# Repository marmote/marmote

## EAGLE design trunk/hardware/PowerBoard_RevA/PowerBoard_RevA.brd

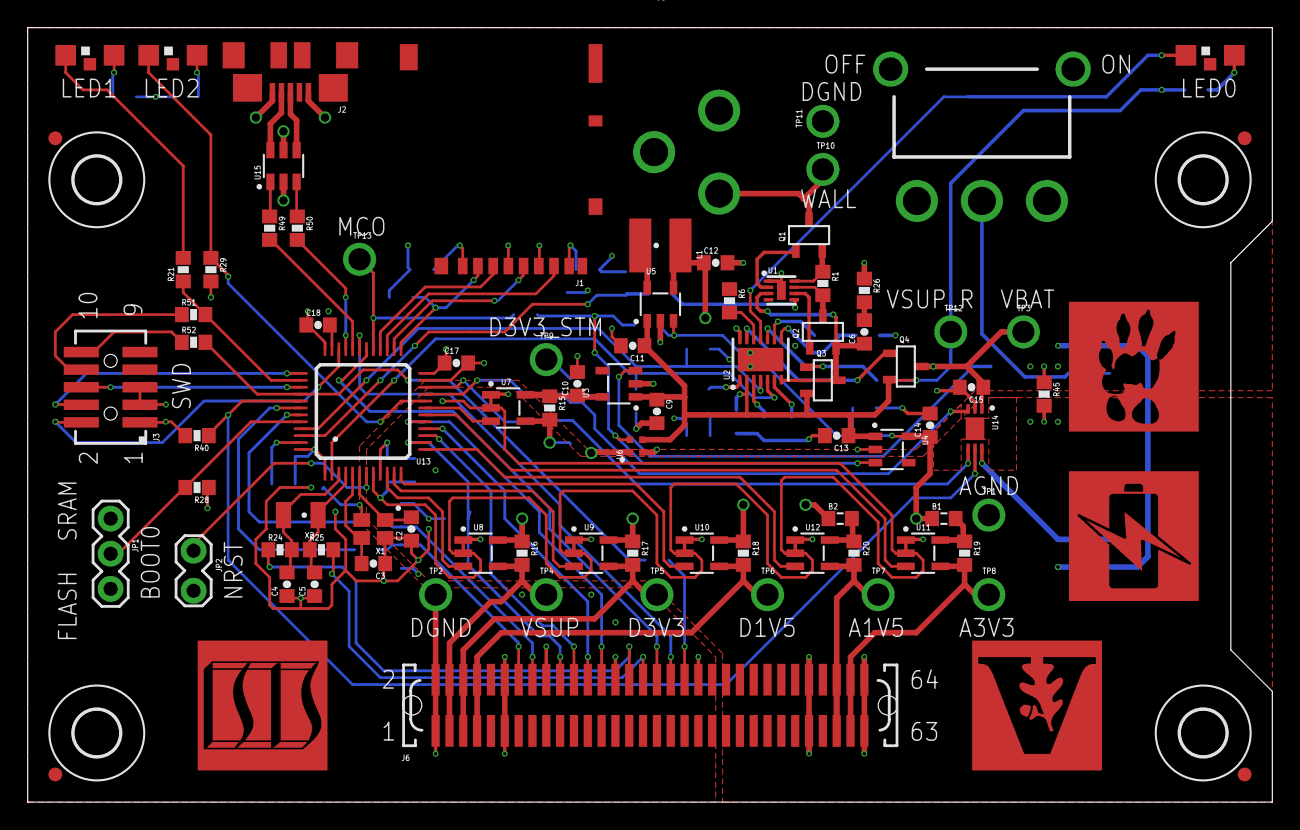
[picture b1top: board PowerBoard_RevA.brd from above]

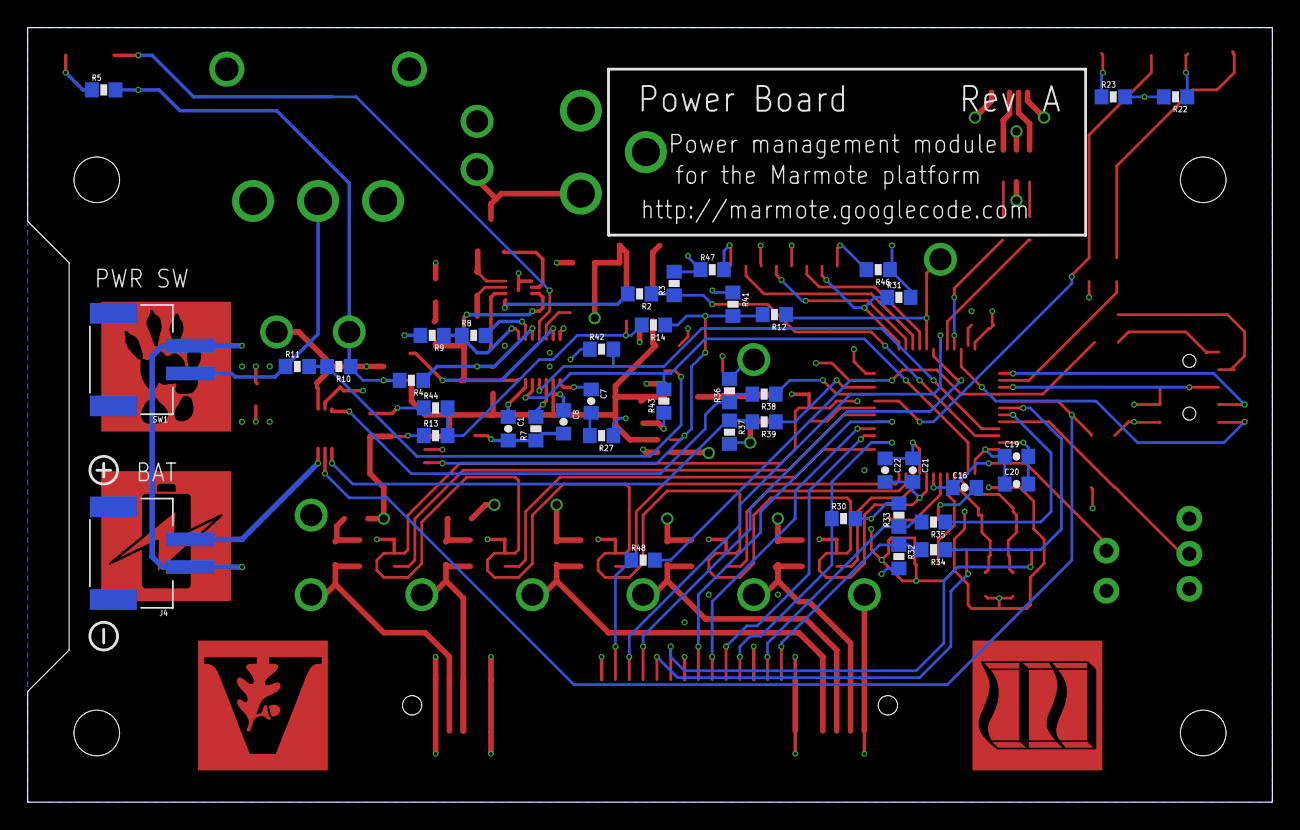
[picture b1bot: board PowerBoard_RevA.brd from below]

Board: 4 copper layers, 90.0 x 56.0 mm, 136 parts (42 on the bottom side), 98 nets.

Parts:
B1, B2: 20m; L0603
C1: 0.15uF; C0603
C2, C3: 10pF; C0603
C4, C5: 4pF; C0603
C6, C9, C12, C13: 10uF; C0603
C7, C8, C10, C11, C14, C20: 4.7uF; C0603
C15, C16, C17, C18, C19: 0.1uF; C0603
C21: 1uF; C0603
C22: 10nF; C0603
J1: CON-HRS-DM3AT; HRS-DM3AT
J2: CON-ZX62R-B-5P; ZX62R-B-5P
J3: CON-FTSH-105-01-L-DV-K; FTSH-105-01-L-DV-K
J4: CON-S2B-PH-SM4-TB; S2B-PH-SM4-TB
J5: CON-PJ-102A; PJ-102A
J6: CON-71436-2164; 71436-XX64
JP1: JUMPER-3PTH; 1X03
JP2: JUMPER-2PTH-LOCK; 1X02-LOCK
L1: 1.6uH; 4X4MM
LED0, LED2: ORANGE; LED1208-RA
LED1: GREEN; LED1208-RA
LOGO1: LOGO-ISIS-600MIL-10MM-CU; LOGO-ISIS-10MM-COPPER
LOGO2: LOGO-VANDERBILT-600MIL-10MM-CU; LOGO-VANDERBILT-10MM-COPPER
LOGO3: LOGO-MARMOTE-600MIL-10MM-CU; LOGO-MARMOTE-10MM-COPPER
LOGO4: LOGO-BATTERY-600MIL-10MM-CU; LOGO-BATTERY-10MM-COPPER
M1, M2, M3, M4: MOUNT-HOLE3.3; 3,3
M5, M6, M7, M8: FIDUCIAL1X2; FIDUCIAL-1X2
Q1: SI2323CDS; SOT23-3L
Q2: SI2312CDS; SOT23-3L
Q3, Q4: SI2333CDS; SOT23-3L
R1, R12, R14, R21, R24, R25, R45, R48: 0; R0603
R2: 1k; R0603
R3, R4, R8, R9: 10k; R0603
R5: 510; R0603
R6, R10, R28, R30, R31, R40, R41, R46, R47: 100k; R0603
R7: 2.1k; R0603
R11, R29, R32, R33, R36, R37: 4.7k; R0603
R13, R42, R43, R44, R51, R52: DNP; R0603
R15, R16, R17, R18, R19, R20: 50m; R0603
R22, R34, R35, R38, R39: 100; R0603
R23: 330; R0603
R26, R27: 1; R0603
R49, R50: 22; R0603
SW1: SWITCH-SPST; S2B-PH-SM4-TB
SW2: SWITCH-MS12ASG30; MS12ASX30
TP1, TP2, TP3, TP4, TP5, TP6, TP7, TP8, TP9, TP10, TP11, TP12, TP13: TESTPOINT
U1: LTC4361-2DC; DFN-8
U2: LTC4085; DFN-14
U3, U4: XC6220B331MR-G; SOT25
U5: XC9236A15DMR-G; SOT25
U6: MIC94043; MLF-4
U7, U8, U9, U10, U11, U12: MAX9938FEUK; SOT23-5L
U13: STM32F10XCXT6; TQFP-48
U14: LTC2942-1; DFN-6
U15: USBLC6-2; SOT23-6L
X1: ECX-2236
X2: ECX-31B

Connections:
!ACPR: Q3.1, R4.1, U2.10
!CHRG: LED0.1, U2.11
!PWRGD: R2.2, U1.5
A1V5: J6.59, J6.60, R20.2, TP7.1, U12.4
A1V5_I: B2.2, R20.1, U12.5
A1V5_SENSE: U12.3, U13.13
A3V3: J6.61, J6.62, R19.2, TP8.1, U11.4
A3V3_I: B1.2, R19.1, U11.5
A3V3_SENSE: U11.3, U13.18
AGND: C21.2, C22.2, J6.55, J6.56, J6.63, J6.64, R45.2, TP1.1, U7.1, U7.2, U8.1, U8.2, U9.1, U9.2, U10.1, U10.2, U11.1, U11.2, U12.1, U12.2, U13.8
BOOT0: JP1.2, R28.2, U13.44
CLPROG: R7.2, U2.3
D1V5: J6.7, J6.8, R18.2, TP6.1, U10.4
D1V5-EN: R13.2, R14.2, R44.2, U5.3
D1V5_I: B2.1, C12.1, L1.2, R18.1, U5.4, U10.5
D1V5_SENSE: U10.3, U13.12
D3V3: J6.5, J6.6, R17.2, TP5.1, U9.4
D3V3_I: B1.1, C14.1, R13.1, R17.1, U4.5, U9.5
D3V3_SENSE: U9.3, U13.11
D3V3_STM: C17.1, C18.1, C19.1, C20.1, C21.1, C22.1, J1.4, J3.1, JP1.1, R3.2, R15.2, R22.2, R23.2, R29.2, R30.2, R31.2, R32.2, R33.2, R36.2, R37.2, R40.2, R46.1, R47.1, TP9.1, U7.4, U13.1, U13.9, U13.24, U13.36, U13.48
D3V3_STM-EN: R10.2, R11.2, U3.3
D3V3_STM-EN-SW: R11.1, SW1.2, SW2.2
D3V3_STM_I: C10.1, R15.1, U3.5, U7.5
D3V3_STM_SENSE: U7.3, U13.19
DGND: C1.2, C2.1, C3.1, C4.1, C5.1, C8.2, C9.2, C10.2, C11.2, C12.2, C13.2, C14.2, C15.2, C16.2, C17.2, C18.2, C19.2, C20.2, J1.6, J2.5, J3.3, J3.5, J4.2, J5.2, J5.3, J6.1, J6.2, J6.11, J6.12, J6.18, J6.28, J6.40, JP1.3, JP2.2, R6.1, R7.1, R9.2, R26.1, R27.1, R28.1, R41.1, R42.1, R43.1, R44.1, R45.1, SW1.1, SW2.1, TP2.1, TP11.1, U1.1, U1.EXP, U2.EXP, U3.2, U4.2, U5.2, U6.2, U13.23, U13.35, U13.47, U14.2, U15.2, X1.2, X1.4
GATE1: Q2.1, U1.6
GATE2: Q4.1, U2.13
GATEP: Q1.1, U1.2
I2C1_SCL: J6.14, R32.1, R34.2
I2C1_SCLI: R34.1, U13.42
I2C1_SDA: J6.16, R33.1, R35.2
I2C1_SDAI: R35.1, U13.43
I2C2_SCL: R36.1, R38.2, U14.3
I2C2_SCLI: R38.1, U13.21
I2C2_SDA: R37.1, R39.2, U14.4
I2C2_SDAI: R39.1, U13.22
IN: Q1.2, R1.1, U1.8
JNTRST: J3.10, R52.1
JTDI: J3.8, R51.1
unnamed: C7.2, R27.2
unnamed: R50.1, U15.3
unnamed: C6.2, R26.2
unnamed: R49.1, U15.1
unnamed: L1.1, U5.5
unnamed: LED0.2, R5.1
unnamed: Q2.3, R1.2, U1.7
unnamed: LED2.2, R23.1
unnamed: J1.1, R46.2
unnamed: LED1.2, R22.1
unnamed: J1.8, R47.2
NRST: C16.1, JP2.1, U13.7
NTC: R8.1, R9.1, U2.8
OSC_IN: C3.2, U13.5, X1.3
OSC_OUT: C2.2, U13.6, X1.1
PA8: R12.1, TP13.1, U13.29
PA8-EN: R12.2, R14.1, R41.2, U4.3, U6.4
PA9: J6.34, U13.30
PA10: J6.36, U13.31
PA15: R21.1, R51.2, U13.38
PA15-LED1: LED1.1, R21.2
PB2: LED2.1, R29.1, U13.20
PB4: R48.2, R52.2, U13.40
PB4-SF: J6.38, R48.1
PB5: R40.1, U13.41, U14.5
PB8: R42.2, U2.4, U13.45
PB9: R2.1, R3.1, U13.46
PC13: R43.2, U2.5, U13.2
PC14: J6.30, R24.1
PC14-S: C4.2, R24.2, U13.3, X2.2
PC15: J6.32, R25.2
PC15-S: C5.2, R25.1, U13.4, X2.1
PROG: R6.2, U2.12
SPI1_MISO: J6.24, U13.16
SPI1_MOSI: J6.26, U13.17
SPI1_NSS: J6.20, R30.1, U13.14
SPI1_SCK: J6.22, U13.15
SPI2_MISO: J1.7, U13.27
SPI2_MOSI: J1.3, U13.28
SPI2_NSS: J1.2, R31.1, U13.25
SPI2_SCK: J1.5, U13.26
SWCLK: J3.4, U13.37
SWDIO: J3.2, U13.34
TIMER: C1.1, U2.6
TRACESWO: J3.6, U13.39
USBD+: J2.3, U15.4
USBD-: J2.2, U15.6
USBDM: R49.2, U13.32
USBDP: R50.2, U13.33
VBAT: C15.1, Q4.3, TP3.1, U2.14, U14.1
VBAT_I: J4.1, U14.6
VBUS: C7.1, J2.1, U2.1, U15.5
VNTC: R8.2, U2.9
VSUP: J6.3, J6.4, R16.2, TP4.1, U8.4
VSUP_I: R16.1, U6.1, U8.5
VSUP_R: C8.1, C9.1, C11.1, C13.1, Q3.2, Q4.2, R4.2, R5.2, R10.1, TP12.1, U2.2, U3.1, U4.1, U5.1, U6.3
VSUP_SENSE: U8.3, U13.10
WALL: J5.1, Q1.3, TP10.1
WALL_P: C6.1, Q2.2, Q3.3, U1.3, U2.7

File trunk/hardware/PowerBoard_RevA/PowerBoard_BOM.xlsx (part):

Bill of Materials for 'Marote - Power Supply Board (Rev A)'
Item # | Reference | Value | Package | Manufacturer | Manufacturer Part # | Supplier | Supplier Part # | Details | Qty | Unit Price | Total Cost
1 | B1, B2 | 20mOhm@DC, 70Ohm@100MHz | BEAD0603 | Murata | BLM18SG700TN1D | Digi-Key | 490-5224-1-ND | FERRITE CHIP 70OHM 4A 0603 | 2 | 0.35299999999999998 | 0.70599999999999996
2 | C4, C5 | DNP | C0603 | TDK | C1608C0G1H040B | Digi-Key | 445-5028-1-ND | CAP CER 4.0PF 50V C0G 0603 | 2 | 0.16 | 0.32
3 | C2, C3 | 10pF | C0603 | TDK | C1608C0G1H100J | Digi-Key | 445-6852-1-ND | CAP CER 10PF 50V C0G 5% 0603 | 2 | 0.12 | 0.24
4 | C22 | 10nF | C0603 | TDK | C1608X7R1E103K | Digi-Key | 445-5100-1-ND | CAP CER 10000PF 25V X7R 10% 0603 | 1 | 0.08 | 0.08
5 | C15, C16, C17, C18, C19 | 0.1uF | C0603 | TDK | C1608X7R1C104K | Digi-Key | 445-1317-1-ND | CAP CER .10UF 16V 10% X7R 0603 | 5 | 0.08 | 0.4
6 | C1 | 0.15uF | C0603 | TDK | C1608X7R1C154K | Digi-Key | 445-5123-1-ND | CAP CER .15UF 16V 10% X7R 0603 | 1 | 0.2 | 0.2
7 | C21 | 1uF | C0603 | TDK | C1608X7R1C105K | Digi-Key | 445-1604-1-ND | CAP CER 1.0UF 16V X7R 10% 0603 | 1 | 0.23 | 0.23
8 | C7, C8, C10, C11, C14, C20 | 4.7uF | C0603 | TDK | C1608X5R0J475K | Digi-Key | 445-5178-1-ND | CAP CER 4.7UF 6.3V X5R 0603 | 6 | 0.36 | 2.16
9 | C6, C9, C12, C13 | 10uF | C0603 | TDK | C1608X5R0J106M | Digi-Key | 445-4112-1-ND | CAP CER 10UF 6.3V X5R 20% 0603 | 4 | 0.46 | 1.84
10 | J1 | CON-HRS-DM3AT | CON-HRS-DM3AT | Hirose | DM3AT-SF-PEJM5 | Digi-Key | HR1964CT-ND | CONN MICRO SD R/A PUSH-PUSH SMD | 1 | 3.01 | 3.01
11 | J2 | CON-ZX62R-B-5P | CON-ZX62R-B-5P | Hirose | ZX62R-B-5P | Digi-Key | H11574CT-ND | CONN RCPT MICRO USB B SMD R/A | 1 | 1.56 | 1.56
12 | J3 | CON-FTSH-105-01-L-DV-K | CON-FTSH-105-01-L-DV-K | Samtec | FTSH-105-01-L-DV-K | Digi-Key | FTSH-105-01-L-DV-K-ND | CONN HEADER 10 POS DUAL .05" SMD | 1 | 3.36 | 3.36
13 | J4, SW1 | CON-S2B-PH-SM4-TB | CON-S2B-PH-SM4-TB | JST | S2B-PH-SM4-TB(LF)(SN) | Digi-Key | 455-1749-1-ND | CONN HEADER PH SIDE 2POS 2MM SMD | 2 | 0.5 | 1
14 | J5 | CON-PJ-102A | CON-PJ-102A | CUI | PJ-102A | Digi-Key | CP-102A-ND | CONN JACK POWER 2.1MM PCB | 1 | 0.8 | 0.8
15 | J6 | CON-71436-2164 | CON-71436-2164 | Molex | 71436-2164 | Digi-Key | WM17200-ND | CONN PLUG 64POS VERT 1MM SMD | 1 | 8.6 | 8.6
16 | JP1 | DNP | JUMPER-3PTH |  |  |  |  |  | 1 |  | 0
17 | JP2 | DNP | JUMPER-2PTH-LOCK |  |  |  |  |  | 1 |  | 0
18 | L1 | 1.6uH | L-VLCF4018T | TDK | VLCF4018T-1R6N1R7-2 | Digi-Key | 445-3171-1-ND | INDUCTOR POWER 1.6UH 1.7A SMD | 1 | 0.72 | 0.72
19 | LED0, LED2 | ORANGE | LED1208-RA | Kingbright | APECVA3010SECK | Digi-Key | 754-1367-1-ND | LED 3X1MM 601NM ORN RA CHIP SMD | 3 | 0.28000000000000003 | 0.84000000000000008
20 | LED1 | GREEN | LED1208-RA | Kingbright | APECVA3010MGC | Digi-Key | 754-1364-1-ND | LED 3.0X1.0MM 568NM GRN RA SMD | 3 | 0.63 | 1.8900000000000001
21 | M1, M2, M3, M4 | MOUNT-HOLE3.3 | MOUNT-HOLE3.3 |  |  |  |  |  | 4 |  | 0
22 | M5, M6, M7, M8 | FIDUCIAL1X2 | FIDUCIAL1X2 |  |  |  |  |  | 4 |  | 0
23 | Q1 | SI2323CDS | SI2323CDS | Vishay | SI2323CDS-T1-GE3 | Digi-Key | SI2323CDS-T1-GE3CT-ND | MOSFET P-CH 20V SOT-23 | 1 | 0.76 | 0.76
24 | Q2 | SI2312CDS | SI2312CDS | Vishay | SI2312CDS-T1-GE3 | Digi-Key | SI2312CDS-T1-GE3CT-ND | MOSFET N-CH 20V SOT-23 | 1 | 0.45 | 0.45
25 | Q3, Q4 | SI2333CDS | SI2333CDS | Vishay | SI2333CDS-T1-GE3 | Digi-Key | SI2333CDS-T1-GE3CT-ND | MOSFET P-CH D-S 12V SOT-23 | 2 | 0.84 | 1.68
26 | R13, R42, R43, R44, R51, R52 | DNP | R0603 |  |  |  |  |  | 6 |  | 0
27 | R1, R12, R14, R21, R24, R25, R45, R48 | 0 | R0603 | Rohm | MCR03EZPJ000 | Digi-Key | RHM0.0GCT-ND | RES 0.0 OHM 1/10W 0603 SMD | 8 | 1.7999999999999999E-2 | 0.14399999999999999
28 | R15, R16, R17, R18, R19, R20 | 50m | R0603 | Vishay | WSL0603R0500FEA18 | Digi-Key | WSLL-.05CT-ND | RES .05 OHM 0.2W 1% 0603 SMD | 6 | 1.32 | 7.92
29 | R26, R27 | 1 | R0603 | Rohm | MCR03EZPJ1R0 | Digi-Key | RHM1.0GCT-ND | RES 1.0 OHM 1/10W 5% 0603 SMD | 2 | 1.7999999999999999E-2 | 3.5999999999999997E-2
30 | R49, R50 | 22 | R0603 | Rohm | MCR03EZPFX22R0 | Digi-Key | RHM22.0HCT-ND | RES 22.0 OHM 1/10W 1% 0603 SMD | 2 | 2.3E-2 | 4.5999999999999999E-2
31 | R22, R34, R35, R38, R39 | 100 | R0603 | Rohm | MCR03EZPJ101 | Digi-Key | RHM100GCT-ND | RES 100 OHM 1/10W 5% 0603 SMD | 4 | 1.7999999999999999E-2 | 7.1999999999999995E-2
32 | R23 | 330 | R0603 | Rohm | MCR03EZPFX3300 | Digi-Key | RHM330HCT-ND | RES 330 OHM 1/10W 1% 0603 SMD | 1 | 2.3E-2 | 2.3E-2
33 | R5 | 510 | R0603 | Rohm | MCR03EZPJ511 | Digi-Key | RHM510GCT-ND | RES 510 OHM 1/10W 5% 0603 SMD | 1 | 1.7999999999999999E-2 | 1.7999999999999999E-2
34 | R2 | 1k | R0603 | Rohm | MCR03EZPJ102 | Digi-Key | RHM1.0KGCT-ND | RES 1.0K OHM 1/10W 5% 0603 SMD | 1 | 1.7999999999999999E-2 | 1.7999999999999999E-2
35 | R7 | 2.1k | R0603 | Rohm | MCR03EZPFX2101 | Digi-Key | RHM2.10KHCT-ND | RES 2.10K OHM 1/10W 1% 0603 SMD | 1 | 2.3E-2 | 2.3E-2
36 | R11, R29, R32, R33, R36, R37 | 4.7k | R0603 | Rohm | MCR03EZPJ472 | Digi-Key | RHM4.7KGCT-ND | RES 4.7K OHM 1/10W 5% 0603 SMD | 6 | 1.7999999999999999E-2 | 0.10799999999999998
37 | R9 | 10k | NTCG06 | Vishay/Dale | NTHS0603N02N1002JE | Digi-Key | 541-1107-1-ND | THERMISTOR NTC 10K OHM 5% 0603 | 1 | 1 | 1
38 | R3, R4, R8 | 10k | R0603 | Rohm | MCR03EZPFX1002 | Digi-Key | RHM10.0KHCT-ND | RES 10.0K OHM 1/10W 1% 0603 SMD | 3 | 2.3E-2 | 6.9000000000000006E-2
39 | R6, R10, R28, R30, R31, R40, R41, R46, R47 | 100k | R0603 | Rohm | MCR03EZPFX1003 | Digi-Key | RHM100KHCT-ND | RES 100K OHM 1/10W 1% 0603 SMD | 9 | 2.3E-2 | 0.20699999999999999
40 | SW2 | SWITCH-MS12ASG30 | SWITCH-MS12ASG30 | NKK | MS12ASG30 | Digi-Key | 360-2390-ND | SW SLIDE SPDT 0.4VA GOLD R/A PC | 1 | 5.45 | 5.45
41 | TP3, TP4, TP5, TP6, TP9, TP10, TP12 | TESTPOINT | TESTPOINT-BLUE | Keystone | 5122 | Digi-Key | 5122K-ND | TEST POINT PC COMPACT T/H BLUE | 7 | 0.38 | 2.66
42 | TP7, TP8 | TESTPOINT | TESTPOINT-GREEN | Keystone | 5121 | Digi-Key | 5121K-ND | TEST POINT PC COMPACT T/H GREEN | 2 | 0.38 | 0.76
43 | TP13 | TESTPOINT | TESTPOINT-RED | Keystone | 5005 | Digi-Key | 5005K-ND | TEST POINT PC COMPACT .063"D RED | 1 | 0.36 | 0.36
44 | TP1, TP2, TP11 | TESTPOINT | TESTPOINT-YELLOW | Keystone | 5009 | Digi-Key | 5009K-ND | TEST POINT PC COMPACT .063"D YLW | 3 | 0.36 | 1.08
45 | U1 | LTC4361-2DC | LTC4361-2DC | Linear Technology | LTC4361IDC-2#TRMPBF | Digi-Key | LTC4361IDC-2#TRMPBFCT-ND | IC OVERVOLTAGE PROT CONT 8-DFN | 1 | 3.78 | 3.78
46 | U13 | STM32F10XCXT6 | STM32F10XCXT6 | STMicroelectronics | STM32F102CBT6 | Digi-Key | 497-8308-ND | MCU ARM 32BIT 128KB FLASH 48LQFP | 1 | 8.9499999999999993 | 8.9499999999999993
47 | U14 | LTC2942-1 | LTC2942-1 | Linear Technology | LTC2942CDCB-1#TRMPBF | Digi-Key | LTC2942CDCB-1#TRMPBFCT-ND | IC FUEL/GAS GAUGE LI-ION 1A 6DFN | 1 | 4.51 | 4.51
48 | U15 | USBLC6-2 | USBLC6-2 | STMicroelectronics | USBLC6-2SC6 | Digi-Key | 497-5235-1-ND | IC ESD PROTECTION LO CAP SOT23-6 | 1 | 1 | 1
49 | U2 | LTC4085 | LTC4085 | Linear Technology | LTC4085EDE#PBF | Digi-Key | LTC4085EDE#PBF-ND | IC USB POWER MANAGER 14-DFN | 1 | 3.3 | 3.3
50 | U3, U4 | XC6220B331MR-G | XC6220B331MR-G | Torex | XC6220B331MR-G | Digi-Key | 893-1133-1-ND | IC REG LDO 3.3V 1A SOT-25 | 2 | 0.88 | 1.76
51 | U5 | XC9236A15DMR-G | XC9236A15DMR-G | Torex | XC9236A15DMR-G | Digi-Key | 893-1120-1-ND | IC BUCK SYNC 1.5V .6A SOT-25 3MHZ | 1 | 1.5 | 1.5
52 | U6 | MIC94043 | MIC94043 | Micrel | MIC94043YFL TR | Digi-Key | 576-3228-1-ND | IC LOAD SW HISIDE 3A 4-MLF | 1 | 1.3 | 1.3
53 | U7, U8, U9, U10, U11, U12 | MAX9938FEUK | MAX9938FEUK | Maxim | MAX9938FEUK+T | Digi-Key | MAX9938FEUK+TCT-ND | IC AMP CURRENT SENSE SOT23-5 | 6 | 1.68 | 10.08
54 | X1 | ECX-2236 | ECX-2236 | ECS | ECS-160-8-36CKM | Digi-Key | XC1552CT-ND | CRYSTAL 16.000 MHZ 8PF SMD | 1 | 3.45 | 3.45
55 | X2 | DNP | ECX-31B | ECS | ECS-.327-7-34B-TR | Digi-Key | XC1656CT-ND | CRYSTAL 32.768 KHZ 7PF SMD | 1 | 1.26 | 1.26
 |  |  |  |  |  |  |  |  |  |  | 0
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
